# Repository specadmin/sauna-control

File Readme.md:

# Sauna control #

This is a control board for the sauna equipment. It includes thermostat and recycling motor control.

| Front side assembly | Back side assembly |
|---|---|
|  |  |

## Get sources ##

```
git clone https://github.com/specadmin/sauna-control
cd sauna-control
git submodule update --init
```

## Compile  ##

`make`

Make sure you have `avr-gcc` and `avr-libc` installed before running this command.

## Upload ##

`make install`

This command uses `avrdude` for uploading the firmware. See Makefile for details.

## Code modification ##

Use Code::Blocks or any other IDE for code modification.

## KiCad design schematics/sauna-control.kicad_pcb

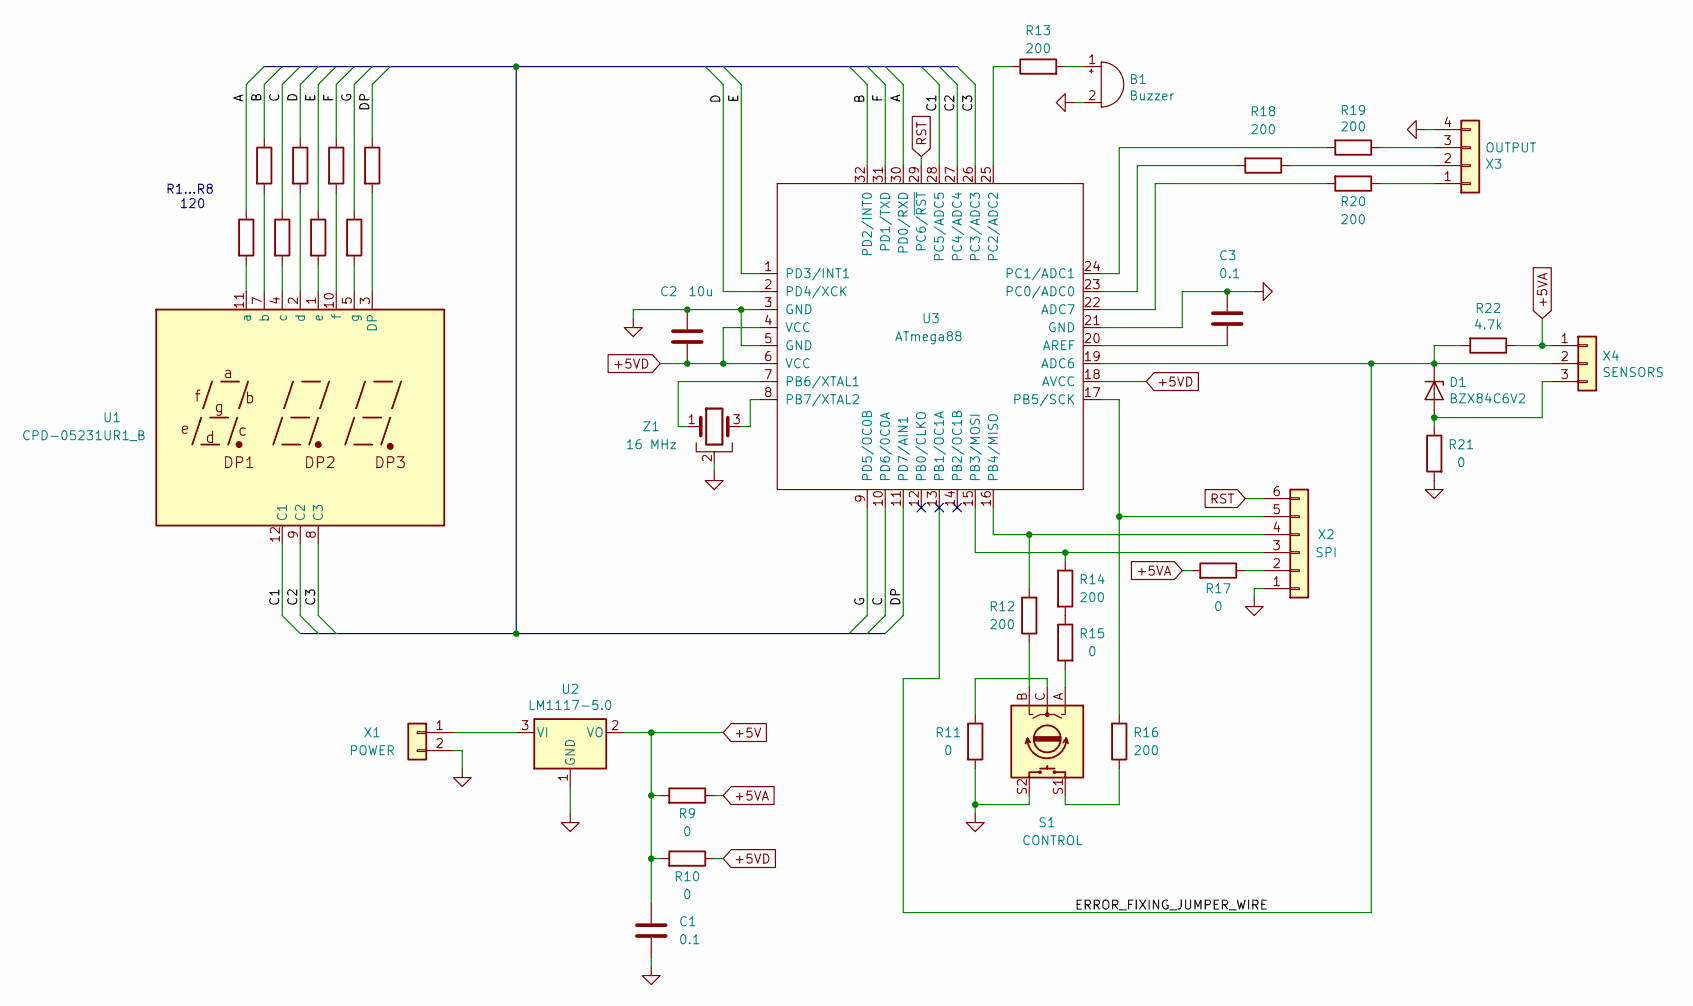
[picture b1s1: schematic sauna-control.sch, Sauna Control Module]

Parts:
B1: Buzzer; Buzzer_12x9.5RM7.6
C1, C3: 0.1; C_0603_1608Metric
C2: 10u; C_0603_1608Metric
D1: BZX84C6V2; D_SOT-23_ANK
R1, R2, R3, R4, R5, R6, R7, R8: 120; R_1206_3216Metric
R9, R10, R11, R15, R17, R21: 0; R_1206_3216Metric
R12, R13, R14, R16: 200; R_1206_3216Metric
R18, R19, R20: 200; R_0603_1608Metric
R22: 4.7k; R_0603_1608Metric
S1: CONTROL; RotaryEncoder_Alps_EC11E-Switch_Vertical_H20mm_CircularMoun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
U1: CPD-05231UR1_B; CPD-05231UR1B
U2: LM1117-5.0; SOT-223-3_TabPin2
U3: ATmega88; TQFP-32_7x7mm_P0.8mm
X1: POWER; PinHeader_1x02_P2.54mm_Horizontal
X2: SPI; PinHeader_1x06_P2.54mm_Horizontal
X3: OUTPUT; PinHeader_1x04_P2.54mm_Horizontal
X4: SENSORS; PinHeader_1x03_P2.54mm_Horizontal
Z1: 16 MHz; Resonator_SMD_muRata_CSTxExxV-3Pin_3.0x1.1mm

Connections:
+5V: C1.2, R9.2, R10.2, U2.2 (VO)
+5VA: R9.1, R17.2, R22.1, X4.1
+5VD: C2.1, R10.1, U3.4 (VCC), U3.6 (VCC), U3.18 (AVCC)
/A: R1.1, U3.30 (PD0/RXD)
/B: R2.1, U3.32 (PD2/INT0)
/C: R3.1, U3.10 (PD6/0C0A)
/C1: U1.12 (C1), U3.28 (PC5/ADC5)
/C2: U1.9 (C2), U3.27 (PC4/ADC4)
/C3: U1.8 (C3), U3.26 (PC3/ADC3)
/D: R4.1, U3.2 (PD4/XCK)
/DP: R8.1, U3.11 (PD7/AIN1)
/E: R5.1, U3.1 (PD3/INT1)
/ERROR_FIXING_JUMPER_WIRE: D1.1 (K), R22.2, U3.13 (PB1/OC1A), U3.19 (ADC6), X4.2
/F: R6.1, U3.31 (PD1/TXD)
/G: R7.1, U3.9 (PD5/OC0B)
GND: B1.2 (+), C1.1, C2.2, C3.2, R11.2, R21.2, S1.S2, U2.1 (GND), U3.3 (GND), U3.5 (GND), U3.21 (GND), X1.2, X2.1, X3.4, Z1.2
unnamed: B1.1 (-), R13.2
unnamed: C3.1, U3.20 (AREF)
unnamed: D1.2 (A), R21.1, X4.3
unnamed: R1.2, U1.11 (a)
unnamed: R2.2, U1.7 (b)
unnamed: R3.2, U1.4 (c)
unnamed: R4.2, U1.2 (d)
unnamed: R5.2, U1.1 (e)
unnamed: R6.2, U1.10 (f)
unnamed: R7.2, U1.5 (g)
unnamed: R8.2, U1.3 (DP)
unnamed: R11.1, S1.C
unnamed: R12.1, S1.B
unnamed: R12.2, U3.16 (PB4/MISO), X2.4
unnamed: R13.1, U3.25 (PC2/ADC2)
unnamed: R14.1, U3.15 (PB3/MOSI), X2.3
unnamed: R14.2, R15.1
unnamed: R15.2, S1.A
unnamed: R16.1, S1.S1
unnamed: R16.2, U3.17 (PB5/SCK), X2.5
unnamed: R17.1, X2.2
unnamed: R18.1, X3.2
unnamed: R18.2, U3.23 (PC0/ADC0)
unnamed: R19.1, X3.3
unnamed: R19.2, U3.24 (PC1/ADC1)
unnamed: R20.1, X3.1
unnamed: R20.2, U3.22 (ADC7)
unnamed: U2.3 (VI), X1.1
unnamed: U3.7 (PB6/XTAL1), Z1.1
unnamed: U3.8 (PB7/XTAL2), Z1.3
RST: U3.29 (PC6/~RST), X2.6

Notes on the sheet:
R1...R8 120

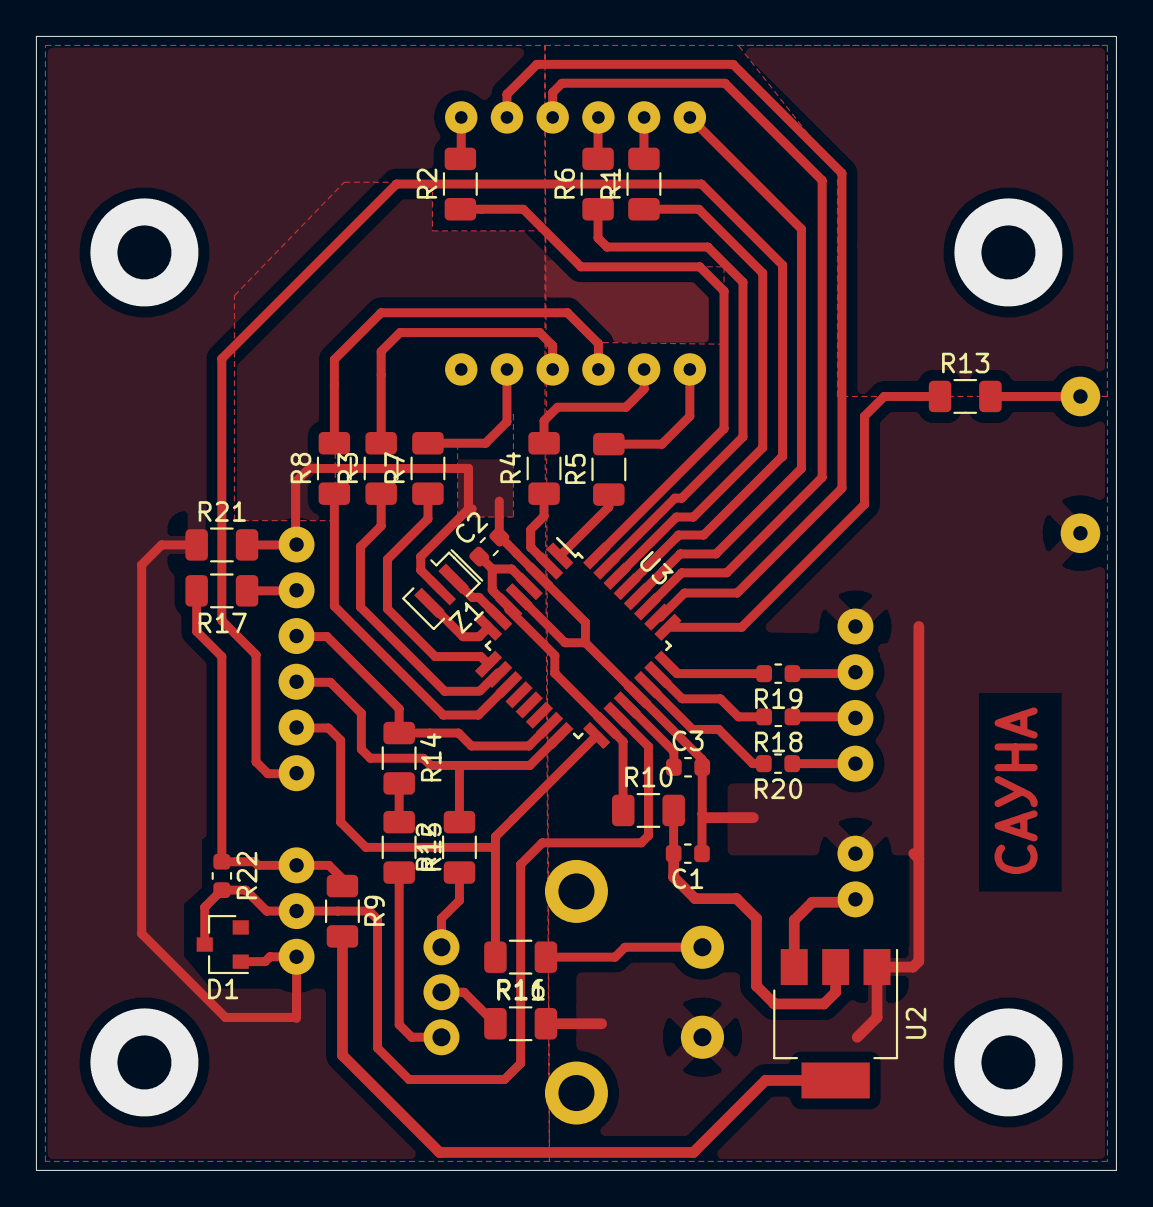
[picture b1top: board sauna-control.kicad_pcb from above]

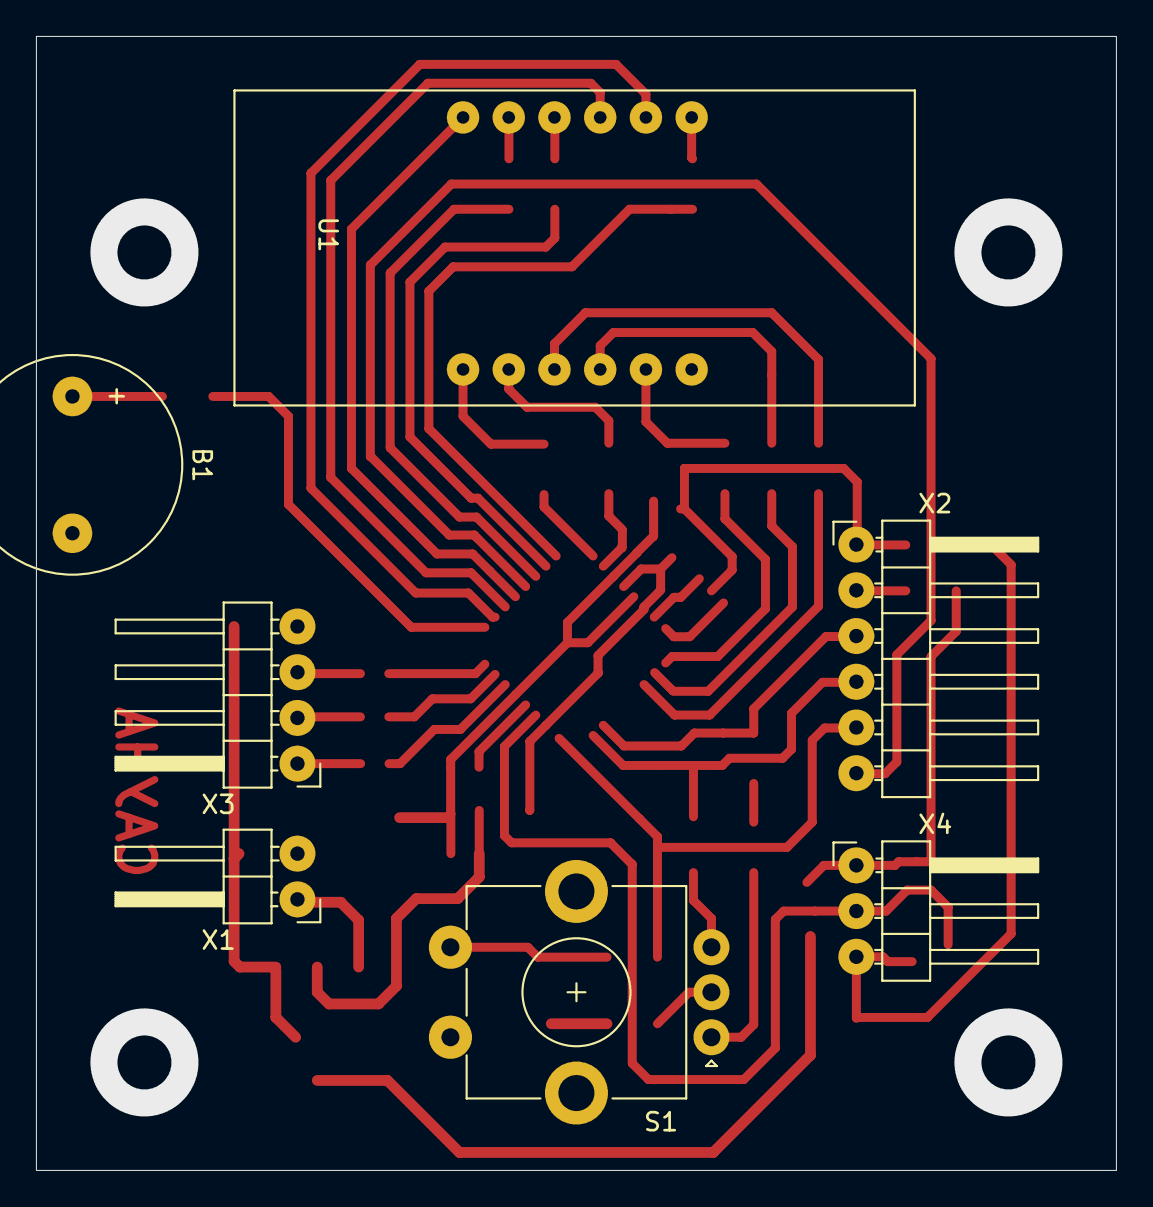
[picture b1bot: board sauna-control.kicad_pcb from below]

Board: 2 copper layers, 60.0 x 63.0 mm, 36 parts (7 on the bottom side), 47 nets.

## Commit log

2020-05-22 First release
2020-05-22 Readme added
2020-05-22 Makefile added
2020-05-22 Images updates
2020-05-23 Documentation improvements
2020-05-23 Display error code before error sound
2020-05-23 Image alignment changed
